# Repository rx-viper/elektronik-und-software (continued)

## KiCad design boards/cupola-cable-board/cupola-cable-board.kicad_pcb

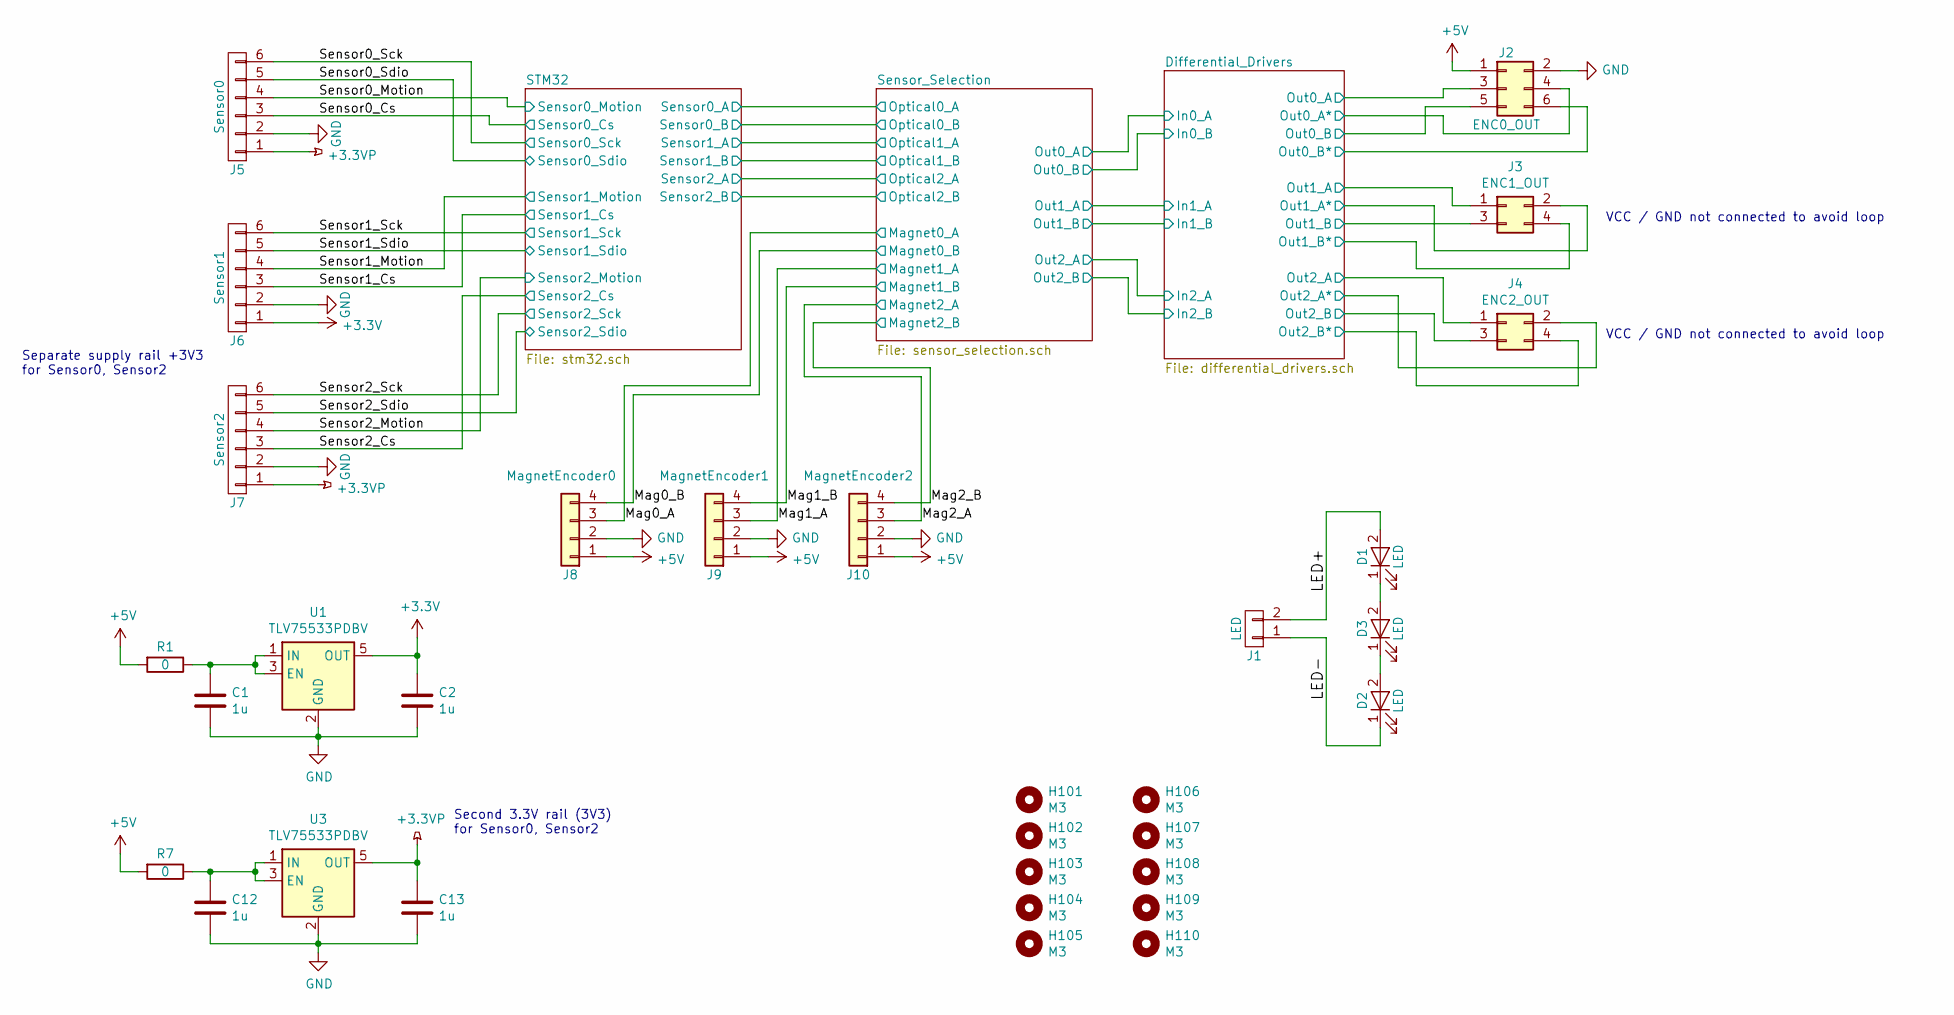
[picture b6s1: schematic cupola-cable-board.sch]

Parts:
C1, C2, C12, C13: 1u; C_0603_1608Metric
D1, D2, D3: LED; LW_G6SP_Handsoldering
H101, H102, H103, H104, H105, H106, H107, H108, H109, H110: M3; MountingHole_3.2mm_M3
J1: LED; PinHeader_1x02_P2.00mm_Vertical
J2: ENC0_OUT; PinHeader_2x03_P2.00mm_Vertical
J3: ENC1_OUT; PinHeader_2x02_P2.00mm_Vertical
J4: ENC2_OUT; PinHeader_2x02_P2.00mm_Vertical
J5: Sensor0; PinHeader_1x06_P2.00mm_Vertical
J6: Sensor1; PinHeader_1x06_P2.00mm_Vertical
J7: Sensor2; PinHeader_1x06_P2.00mm_Vertical
J8: MagnetEncoder0; PinHeader_1x04_P2.00mm_Vertical
J9: MagnetEncoder1; PinHeader_1x04_P2.00mm_Vertical
J10: MagnetEncoder2; PinHeader_1x04_P2.00mm_Vertical
R1, R7: 0; R_0603_1608Metric
U1, U3: TLV75533PDBV; SOT-23-5

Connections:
+3.3VP: C13.1, J5.1, J7.1, U3.5 (OUT)
+3V3: C2.1, J6.1, U1.5 (OUT); also elsewhere on the board
+5V: J2.1, J8.1, J9.1, J10.1, R1.2, R7.2; also elsewhere on the board
/Differential_Drivers/Out0_A: J2.3; also elsewhere on the board
/Differential_Drivers/Out0_A*: J2.4; also elsewhere on the board
/Differential_Drivers/Out0_B: J2.5; also elsewhere on the board
/Differential_Drivers/Out0_B*: J2.6; also elsewhere on the board
/Differential_Drivers/Out1_A: J3.1; also elsewhere on the board
/Differential_Drivers/Out1_A*: J3.2; also elsewhere on the board
/Differential_Drivers/Out1_B: J3.3; also elsewhere on the board
/Differential_Drivers/Out1_B*: J3.4; also elsewhere on the board
/Differential_Drivers/Out2_A: J4.1; also elsewhere on the board
/Differential_Drivers/Out2_A*: J4.2; also elsewhere on the board
/Differential_Drivers/Out2_B: J4.3; also elsewhere on the board
/Differential_Drivers/Out2_B*: J4.4; also elsewhere on the board
/LED+: D1.2 (A), J1.2
/LED-: D2.1 (K), J1.1
/Mag0_A: J8.3; also elsewhere on the board
/Mag0_B: J8.4; also elsewhere on the board
/Mag1_A: J9.3; also elsewhere on the board
/Mag1_B: J9.4; also elsewhere on the board
/Mag2_A: J10.3; also elsewhere on the board
/Mag2_B: J10.4; also elsewhere on the board
/Sensor0_Cs: J5.3; also elsewhere on the board
/Sensor0_Motion: J5.4; also elsewhere on the board
/Sensor0_Sck: J5.6; also elsewhere on the board
/Sensor0_Sdio: J5.5; also elsewhere on the board
/Sensor1_Cs: J6.3; also elsewhere on the board
/Sensor1_Motion: J6.4; also elsewhere on the board
/Sensor1_Sck: J6.6; also elsewhere on the board
/Sensor1_Sdio: J6.5; also elsewhere on the board
/Sensor2_Cs: J7.3; also elsewhere on the board
/Sensor2_Motion: J7.4; also elsewhere on the board
/Sensor2_Sck: J7.6; also elsewhere on the board
/Sensor2_Sdio: J7.5; also elsewhere on the board
GND: C1.2, C2.2, C12.2, C13.2, J2.2, J5.2, J6.2, J7.2, J8.2, J9.2, J10.2, U1.2 (GND), U3.2 (GND); also elsewhere on the board
unnamed: C1.1, R1.1, U1.1 (IN), U1.3 (EN)
unnamed: C12.1, R7.1, U3.1 (IN), U3.3 (EN)
unnamed: D1.1 (K), D3.2 (A)
unnamed: D2.2 (A), D3.1 (K)

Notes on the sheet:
VCC / GND not connected to avoid loop
Second 3.3V rail (3V3) for Sensor0, Sensor2
Separate supply rail +3V3 for Sensor0, Sensor2

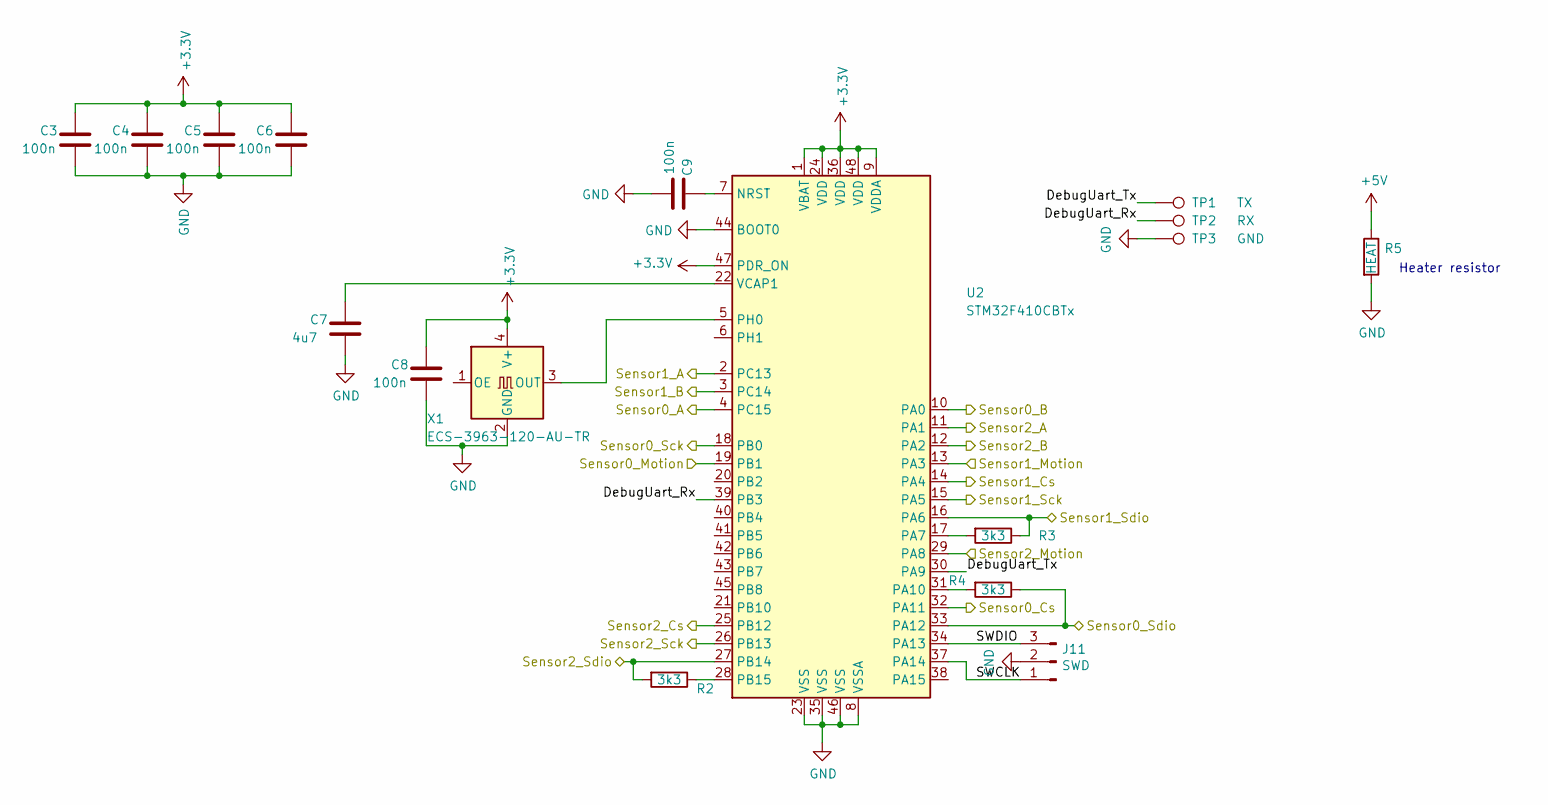
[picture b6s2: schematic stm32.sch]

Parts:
C3, C4, C5, C6, C8, C9: 100n; C_0603_1608Metric
C7: 4u7; C_0805_2012Metric
J11: SWD; PinHeader_1x03_P2.54mm_Vertical
R2, R3, R4: 3k3; R_0603_1608Metric
R5: HEAT; R_0805_2012Metric
TP1: TX; TestPoint_THTPad_D1.5mm_Drill0.7mm
TP2: RX; TestPoint_THTPad_D1.5mm_Drill0.7mm
TP3: GND; TestPoint_THTPad_D1.5mm_Drill0.7mm
U2: STM32F410CBTx; LQFP-48_7x7mm_P0.5mm
X1: ECS-3963-120-AU-TR; Oscillator_SMD_SeikoEpson_SG8002LB-4Pin_5.0x3.2mm

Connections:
+3V3: C3.1, C4.1, C5.1, C6.1, C8.1, U2.1 (VBAT), U2.9 (VDDA), U2.24 (VDD), U2.36 (VDD), U2.47 (PDR_ON), U2.48 (VDD), X1.4 (V+); also elsewhere on the board
+5V: R5.1; also elsewhere on the board
/STM32/DebugUart_Rx: TP2.1, U2.39 (PB3)
/STM32/DebugUart_Tx: TP1.1, U2.30 (PA9)
/STM32/SWCLK: J11.1, U2.37 (PA14)
/STM32/SWDIO: J11.3, U2.34 (PA13)
/Sensor0_Cs: U2.32 (PA11); also elsewhere on the board
/Sensor0_Motion: U2.19 (PB1); also elsewhere on the board
/Sensor0_Sck: U2.18 (PB0); also elsewhere on the board
/Sensor0_Sdio: R4.1, U2.33 (PA12); also elsewhere on the board
/Sensor1_Cs: U2.14 (PA4); also elsewhere on the board
/Sensor1_Motion: U2.13 (PA3); also elsewhere on the board
/Sensor1_Sck: U2.15 (PA5); also elsewhere on the board
/Sensor1_Sdio: R3.1, U2.16 (PA6); also elsewhere on the board
/Sensor2_Cs: U2.25 (PB12); also elsewhere on the board
/Sensor2_Motion: U2.29 (PA8); also elsewhere on the board
/Sensor2_Sck: U2.26 (PB13); also elsewhere on the board
/Sensor2_Sdio: R2.2, U2.27 (PB14); also elsewhere on the board
/Sensor_Selection/Optical0_A: U2.4 (PC15); also elsewhere on the board
/Sensor_Selection/Optical0_B: U2.10 (PA0); also elsewhere on the board
/Sensor_Selection/Optical1_A: U2.2 (PC13); also elsewhere on the board
/Sensor_Selection/Optical1_B: U2.3 (PC14); also elsewhere on the board
/Sensor_Selection/Optical2_A: U2.11 (PA1); also elsewhere on the board
/Sensor_Selection/Optical2_B: U2.12 (PA2); also elsewhere on the board
GND: C3.2, C4.2, C5.2, C6.2, C7.2, C8.2, C9.2, J11.2, R5.2, TP3.1, U2.8 (VSSA), U2.23 (VSS), U2.35 (VSS), U2.44 (BOOT0), U2.46 (VSS), X1.2 (GND); also elsewhere on the board
unnamed: C7.1, U2.22 (VCAP1)
unnamed: C9.1, U2.7 (NRST)
unnamed: R2.1, U2.28 (PB15)
unnamed: R3.2, U2.17 (PA7)
unnamed: R4.2, U2.31 (PA10)
unnamed: U2.5 (PH0), X1.3 (OUT)

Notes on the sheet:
Heater resistor

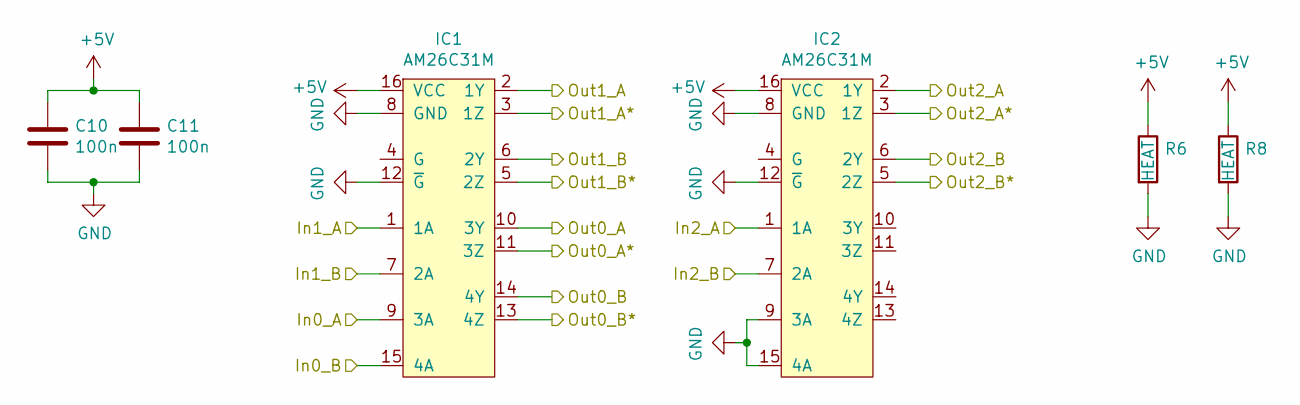
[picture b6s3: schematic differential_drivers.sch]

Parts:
C10, C11: 100n; C_0603_1608Metric
IC1, IC2: AM26C31M; SOIC-16_3.9x9.9mm_P1.27mm; Farnell 4975637
R6, R8: HEAT; R_0805_2012Metric

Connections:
+5V: C10.1, C11.1, IC1.16 (VCC), IC2.16 (VCC), R6.1, R8.1; also elsewhere on the board
/Differential_Drivers/In0_A: IC1.9 (3A); also elsewhere on the board
/Differential_Drivers/In0_B: IC1.15 (4A); also elsewhere on the board
/Differential_Drivers/In1_A: IC1.1 (1A); also elsewhere on the board
/Differential_Drivers/In1_B: IC1.7 (2A); also elsewhere on the board
/Differential_Drivers/In2_A: IC2.1 (1A); also elsewhere on the board
/Differential_Drivers/In2_B: IC2.7 (2A); also elsewhere on the board
/Differential_Drivers/Out0_A: IC1.10 (3Y); also elsewhere on the board
/Differential_Drivers/Out0_A*: IC1.11 (3Z); also elsewhere on the board
/Differential_Drivers/Out0_B: IC1.14 (4Y); also elsewhere on the board
/Differential_Drivers/Out0_B*: IC1.13 (4Z); also elsewhere on the board
/Differential_Drivers/Out1_A: IC1.2 (1Y); also elsewhere on the board
/Differential_Drivers/Out1_A*: IC1.3 (1Z); also elsewhere on the board
/Differential_Drivers/Out1_B: IC1.6 (2Y); also elsewhere on the board
/Differential_Drivers/Out1_B*: IC1.5 (2Z); also elsewhere on the board
/Differential_Drivers/Out2_A: IC2.2 (1Y); also elsewhere on the board
/Differential_Drivers/Out2_A*: IC2.3 (1Z); also elsewhere on the board
/Differential_Drivers/Out2_B: IC2.6 (2Y); also elsewhere on the board
/Differential_Drivers/Out2_B*: IC2.5 (2Z); also elsewhere on the board
GND: C10.2, C11.2, IC1.8 (GND), IC1.12 (~G), IC2.8 (GND), IC2.9 (3A), IC2.12 (~G), IC2.15 (4A), R6.2, R8.2; also elsewhere on the board

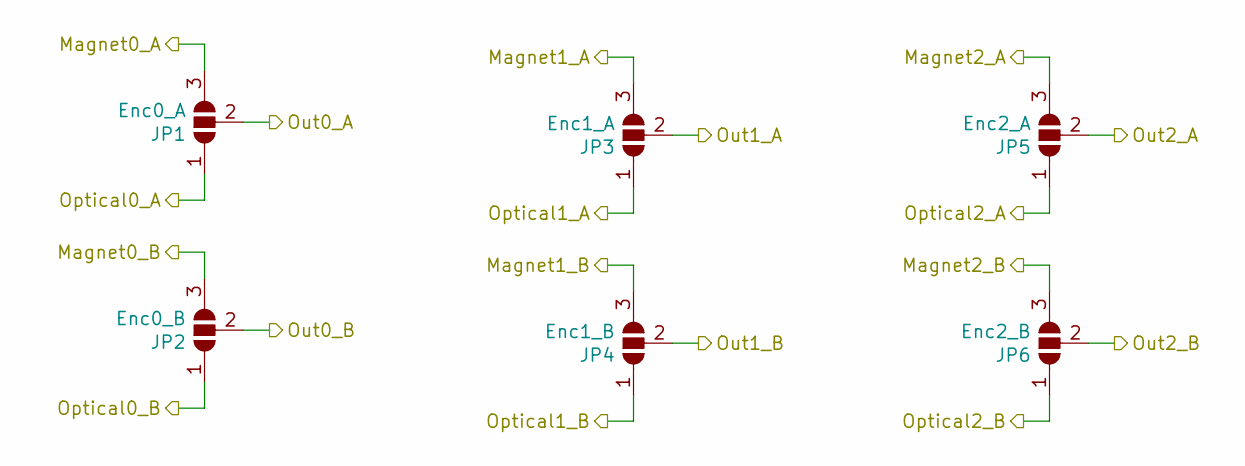
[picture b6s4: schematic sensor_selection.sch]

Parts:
JP1: Enc0_A; SolderJumper-3_P1.3mm_Open_RoundedPad1.0x1.5mm
JP2: Enc0_B; SolderJumper-3_P1.3mm_Open_RoundedPad1.0x1.5mm
JP3: Enc1_A; SolderJumper-3_P1.3mm_Open_RoundedPad1.0x1.5mm
JP4: Enc1_B; SolderJumper-3_P1.3mm_Open_RoundedPad1.0x1.5mm
JP5: Enc2_A; SolderJumper-3_P1.3mm_Open_RoundedPad1.0x1.5mm
JP6: Enc2_B; SolderJumper-3_P1.3mm_Open_RoundedPad1.0x1.5mm

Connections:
/Differential_Drivers/In0_A: JP1.2 (C); also elsewhere on the board
/Differential_Drivers/In0_B: JP2.2 (C); also elsewhere on the board
/Differential_Drivers/In1_A: JP3.2 (C); also elsewhere on the board
/Differential_Drivers/In1_B: JP4.2 (C); also elsewhere on the board
/Differential_Drivers/In2_A: JP5.2 (C); also elsewhere on the board
/Differential_Drivers/In2_B: JP6.2 (C); also elsewhere on the board
/Mag0_A: JP1.3 (B); also elsewhere on the board
/Mag0_B: JP2.3 (B); also elsewhere on the board
/Mag1_A: JP3.3 (B); also elsewhere on the board
/Mag1_B: JP4.3 (B); also elsewhere on the board
/Mag2_A: JP5.3 (B); also elsewhere on the board
/Mag2_B: JP6.3 (B); also elsewhere on the board
/Sensor_Selection/Optical0_A: JP1.1 (A); also elsewhere on the board
/Sensor_Selection/Optical0_B: JP2.1 (A); also elsewhere on the board
/Sensor_Selection/Optical1_A: JP3.1 (A); also elsewhere on the board
/Sensor_Selection/Optical1_B: JP4.1 (A); also elsewhere on the board
/Sensor_Selection/Optical2_A: JP5.1 (A); also elsewhere on the board
/Sensor_Selection/Optical2_B: JP6.1 (A); also elsewhere on the board

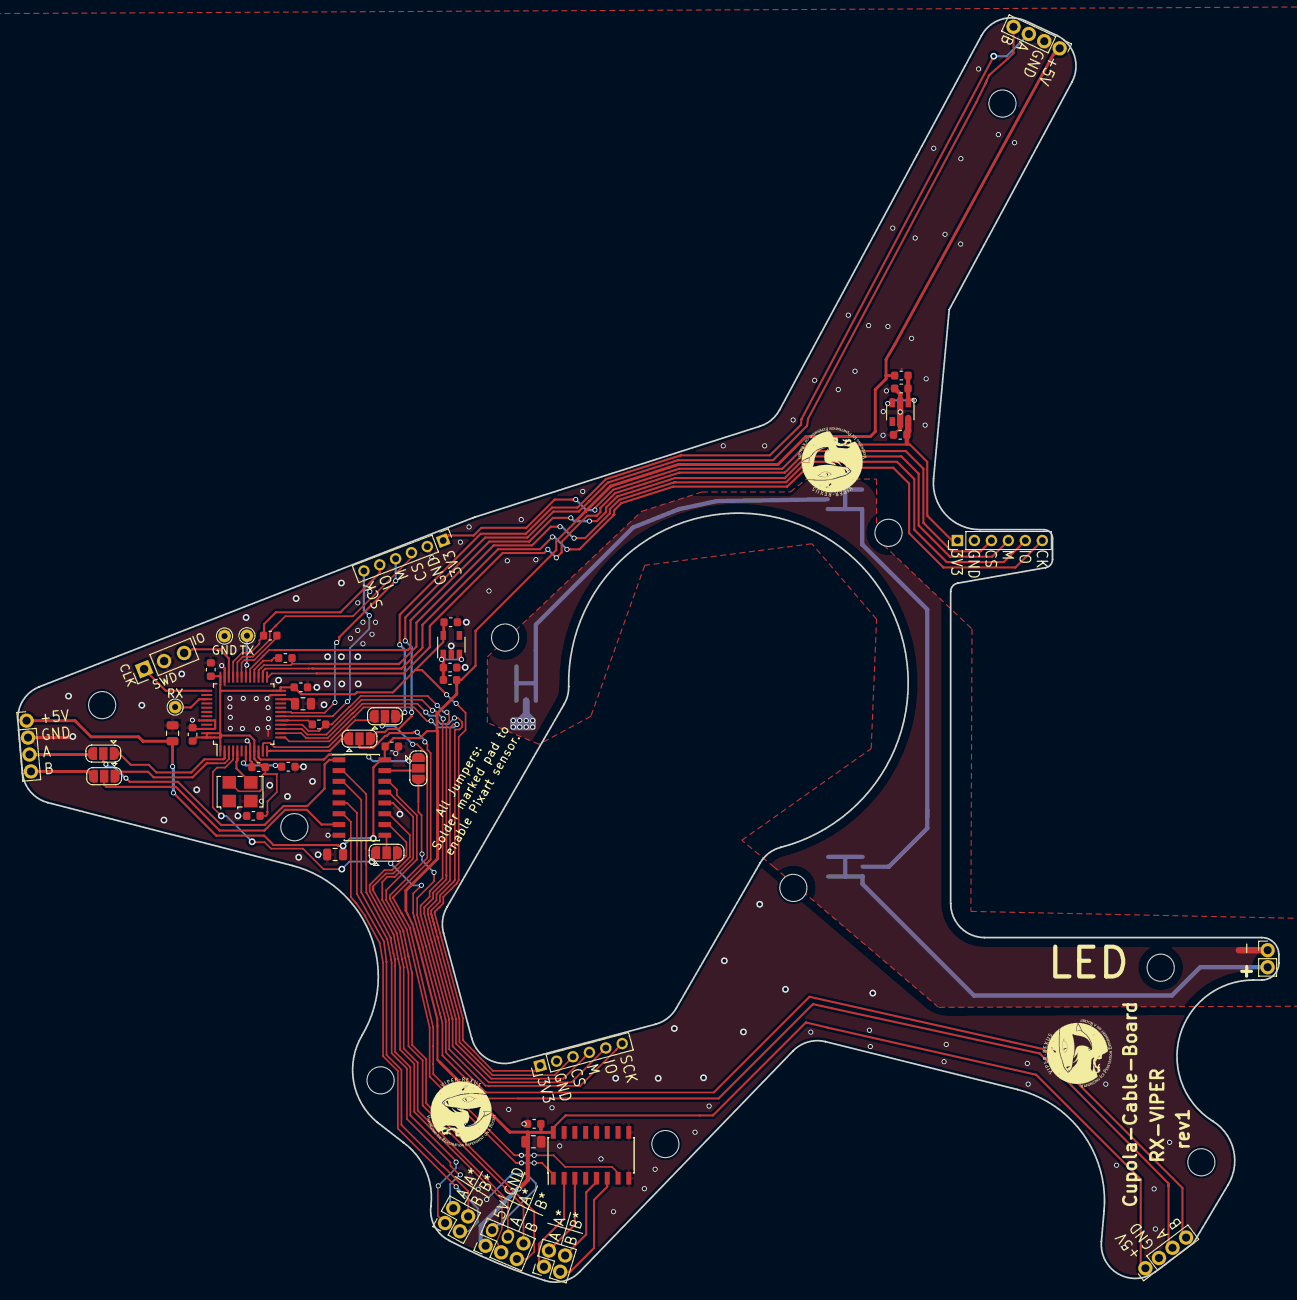
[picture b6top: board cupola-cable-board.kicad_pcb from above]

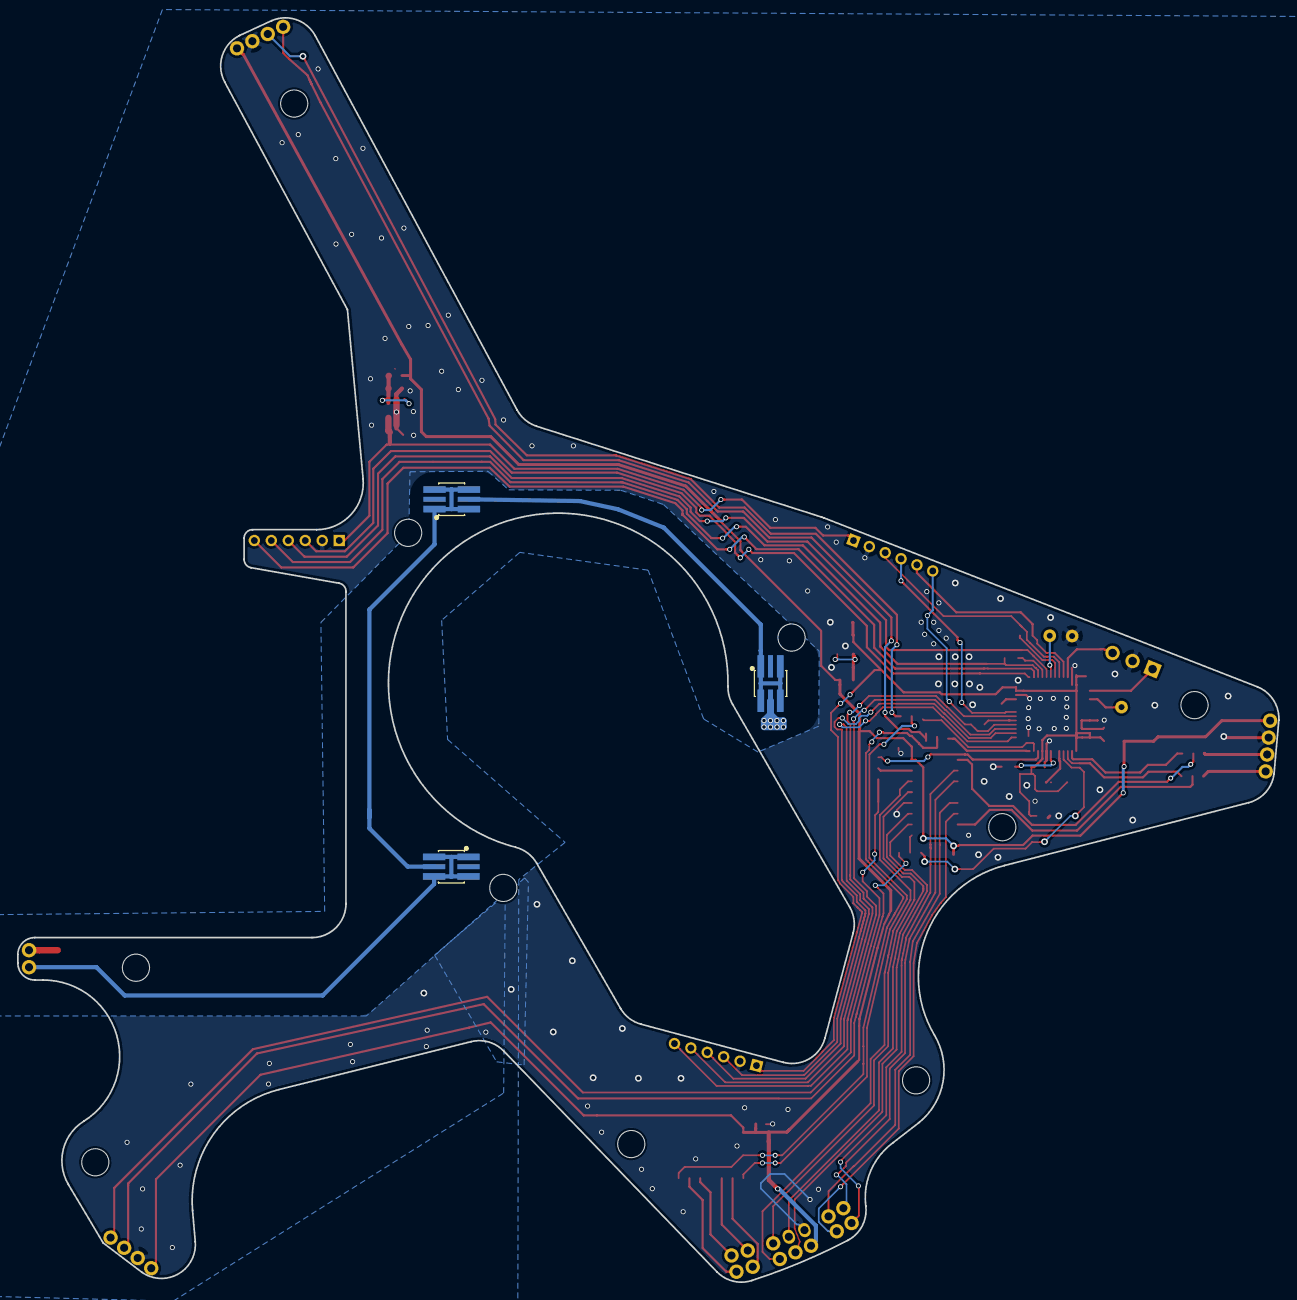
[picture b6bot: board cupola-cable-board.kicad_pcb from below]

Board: 2 copper layers, 148.5 x 148.9 mm, 60 parts (3 on the bottom side), 62 nets.

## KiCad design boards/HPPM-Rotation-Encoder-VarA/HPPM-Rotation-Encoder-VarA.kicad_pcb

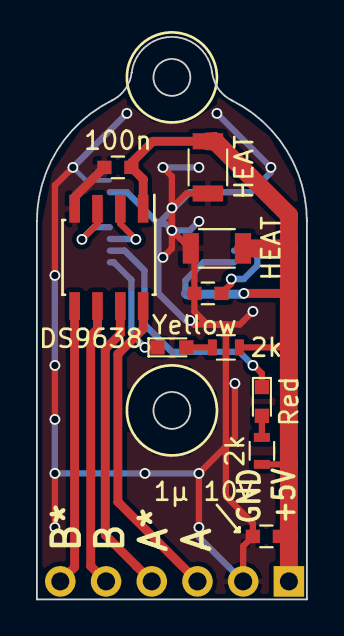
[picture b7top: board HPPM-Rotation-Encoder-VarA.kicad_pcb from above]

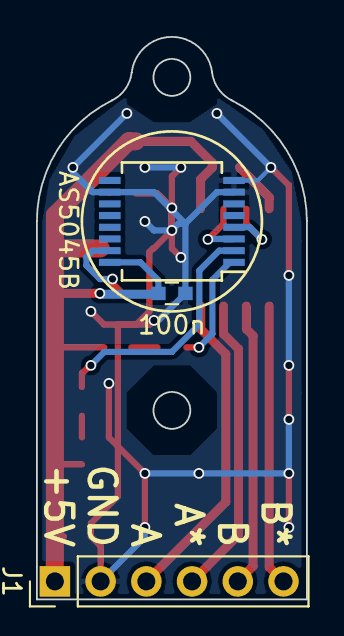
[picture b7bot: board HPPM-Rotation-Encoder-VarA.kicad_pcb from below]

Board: 2 copper layers, 15.0 x 31.2 mm, 13 parts (3 on the bottom side), 13 nets.

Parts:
C1, C3: 100n; C_0603
C2: 4µ7 6V3; C_0603
C4: 1µ 10V; C_0603
D1: Yellow; LED_0603
D2: Red; LED_0603
J1: CONN; Pin_Header_Straight_1x06_Pitch2.54mm
R1, R2: 2k; R_0603
R3, R4: HEAT; R_1206
U1: AS5045B; SSOP-16_5.3x6.2mm_Pitch0.65mm
U2: DS9638; SOIC-8_3.9x4.9mm_Pitch1.27mm

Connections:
+5V: C1.1, C3.1, C4.1, J1.1, R1.2, R2.2, R3.1, R4.1, U1.16, U2.1
/A: J1.3, U2.8
/A*: J1.4, U2.7
/B: J1.5, U2.6
/B*: J1.6, U2.5
/_A: U1.3, U2.2
/_B: U1.4, U2.3
GND: C1.2, C2.2, C3.2, C4.2, J1.2, R3.2, R4.2, U1.7, U1.8, U1.10, U2.4
unnamed: C2.1, U1.15
unnamed: D1.1, U1.1
unnamed: D1.2, R1.1
unnamed: D2.1, U1.2
unnamed: D2.2, R2.1

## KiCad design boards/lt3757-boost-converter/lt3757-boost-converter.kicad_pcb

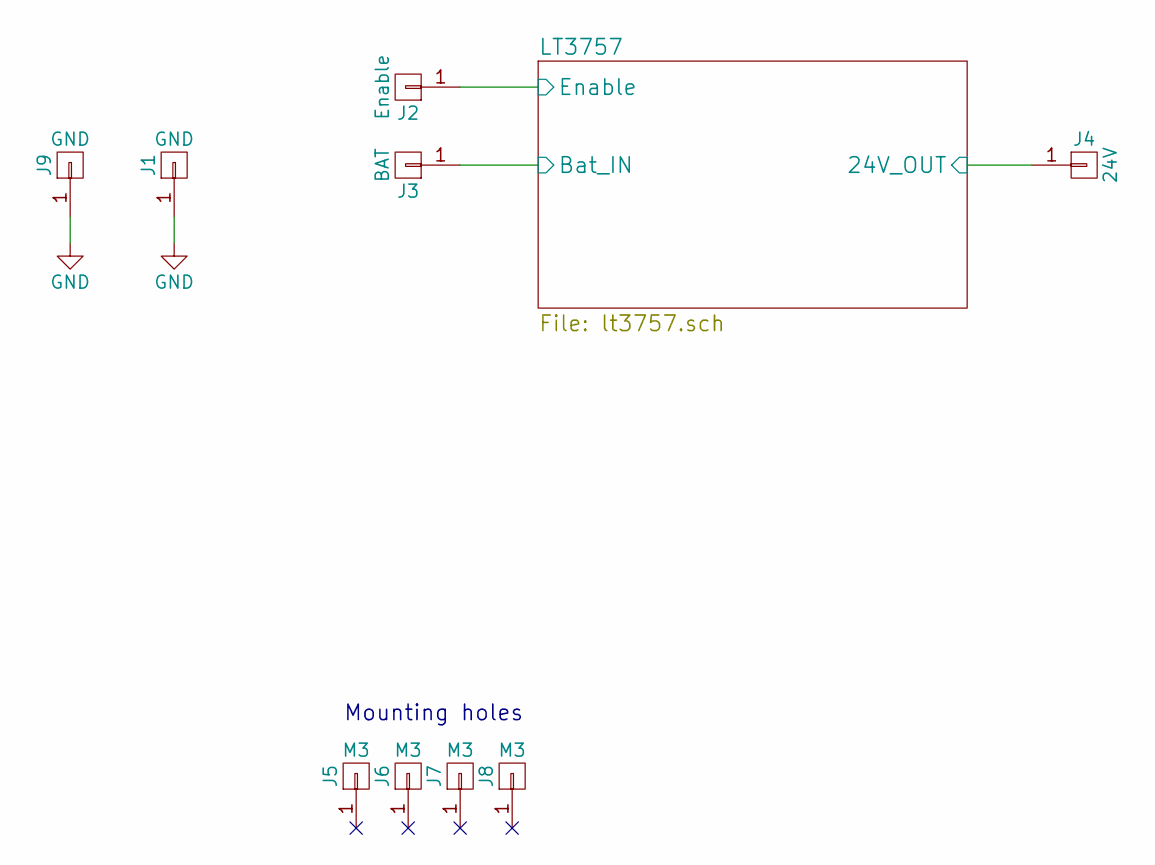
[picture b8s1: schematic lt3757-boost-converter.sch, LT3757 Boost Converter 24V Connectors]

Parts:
J1, J9: GND; MountingHole_3.2mm_M3_Pad
J2: Enable; Measurement_Point_Round-SMD-Pad_Small
J3: BAT; MountingHole_3.2mm_M3_Pad
J4: 24V; MountingHole_3.2mm_M3_Pad
J5, J6, J7, J8: M3; MountingHole_3.2mm_M3

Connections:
/LT3757/24V_OUT: J4.1; also elsewhere on the board
/LT3757/Bat_IN: J3.1; also elsewhere on the board
/LT3757/Enable: J2.1; also elsewhere on the board
GND: J1.1, J9.1; also elsewhere on the board

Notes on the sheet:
Mounting holes

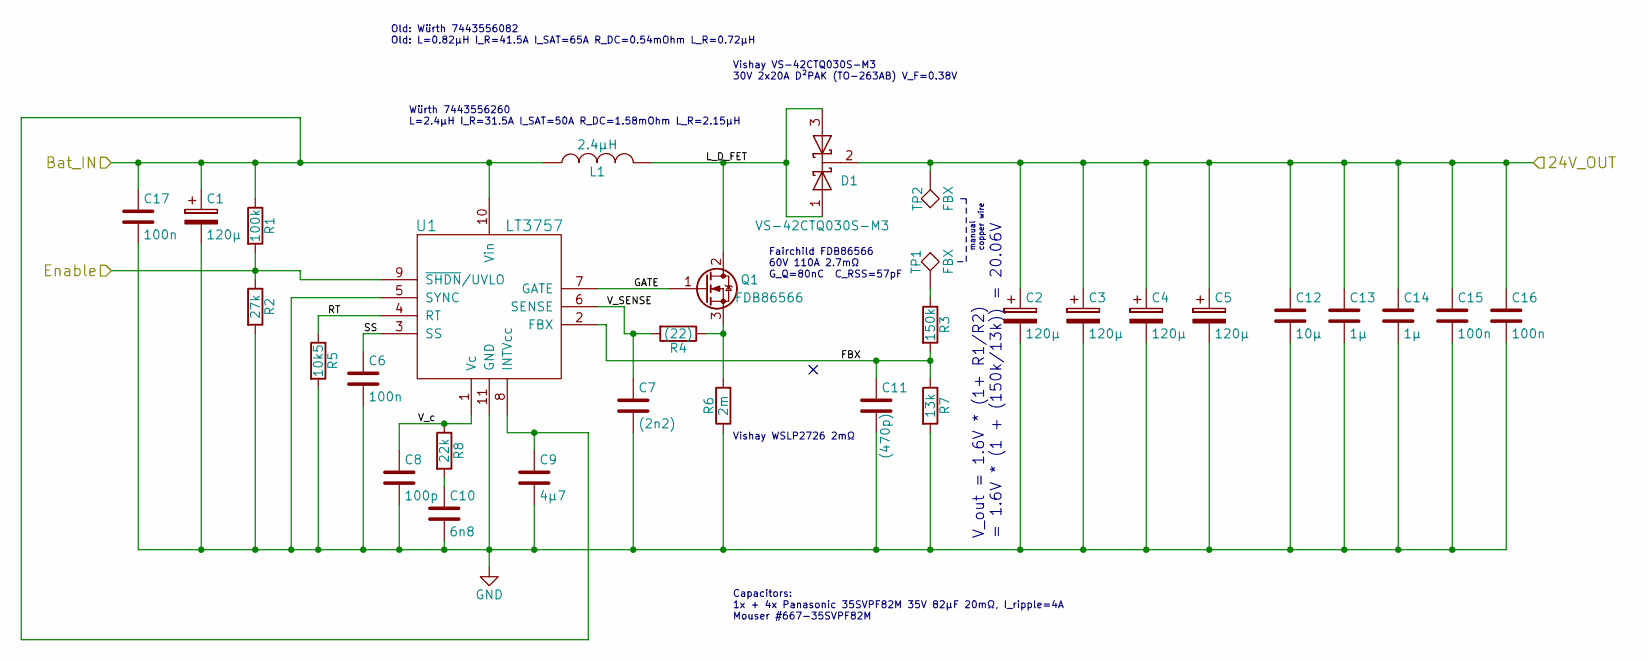
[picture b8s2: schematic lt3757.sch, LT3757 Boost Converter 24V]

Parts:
C1, C2, C3, C4, C5: 120µ; CP_Elec_10x10.5
C6, C15, C16, C17: 100n; C_0603_HandSoldering
C7: (2n2); C_0603_HandSoldering
C8: 100p; C_0603_HandSoldering
C9: 4µ7; C_0805_HandSoldering
C10: 6n8; C_0603_HandSoldering
C11: (470p); C_0603_HandSoldering
C12: 10µ; C_0603_HandSoldering
C13, C14: 1µ; C_0603_HandSoldering
D1: VS-42CTQ030S-M3; TO-263-3Lead
L1: 2.4µH; Inductor_Wurth_HCI-1890
Q1: FDB86566; TO-263-3Lead
R1: 100k; R_0603_HandSoldering
R2: 27k; R_0603_HandSoldering
R3: 150k; R_0603_HandSoldering
R4: (22); R_0603_HandSoldering
R5: 10k5; R_0603_HandSoldering
R6: 2m; WSLP2726
R7: 13k; R_0603_HandSoldering
R8: 22k; R_0603_HandSoldering
TP1, TP2: FBX; Measurement_Point_Round-SMD-Pad_Small
U1: LT3757; MSOP-10-1EP_3x3mm_Pitch0.5mm

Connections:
/LT3757/24V_OUT: C2.1, C3.1, C4.1, C5.1, C12.1, C13.1, C14.1, C15.1, C16.1, D1.2 (K), TP2.1; also elsewhere on the board
/LT3757/Bat_IN: C1.1, C9.1, C17.1, L1.1, R1.1, U1.8 (INTVcc), U1.10 (Vin); also elsewhere on the board
/LT3757/Enable: R1.2, R2.1, U1.9 (~SHDN~/UVLO); also elsewhere on the board
/LT3757/FBX: C11.1, R3.2, R7.1, U1.2 (FBX)
/LT3757/GATE: Q1.1 (G), U1.7 (GATE)
/LT3757/L_D_FET: D1.1 (A), D1.3 (A), L1.2, Q1.2 (D)
/LT3757/RT: R5.1, U1.4 (RT)
/LT3757/SS: C6.1, U1.3 (SS)
/LT3757/V_SENSE: C7.1, R4.2, U1.6 (SENSE)
/LT3757/V_c: C8.1, R8.1, U1.1 (Vc)
GND: C1.2, C2.2, C3.2, C4.2, C5.2, C6.2, C7.2, C8.2, C9.2, C10.2, C11.2, C12.2, C13.2, C14.2, C15.2, C16.2, C17.2, R2.2, R5.2, R6.1, R7.2, U1.5 (SYNC), U1.11 (GND); also elsewhere on the board
unnamed: C10.1, R8.2
unnamed: Q1.3 (S), R4.1, R6.2
unnamed: R3.1, TP1.1

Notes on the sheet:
Würth 7443556260 L=2.4µH I_R=31.5A I_SAT=50A R_DC=1.58mOhm L_R=2.15µH
Vishay VS-42CTQ030S-M3 30V 2x20A D²PAK (TO-263AB) V_F=0.38V
Capacitors: 1x + 4x Panasonic 35SVPF82M 35V 82µF 20mΩ, I_ripple=4A Mouser #667-35SVPF82M
Vishay WSLP2726 2mΩ
Fairchild FDB86566 60V 110A 2.7mΩ G_Q=80nC C_RSS=57pF
Old: Würth 7443556082 Old: L=0.82µH I_R=41.5A I_SAT=65A R_DC=0.54mOhm L_R=0.72µH
manual copper wire
V_out = 1.6V * (1+ R1/R2) = 1.6V * (1 + (150k/13k)) = 20.06V

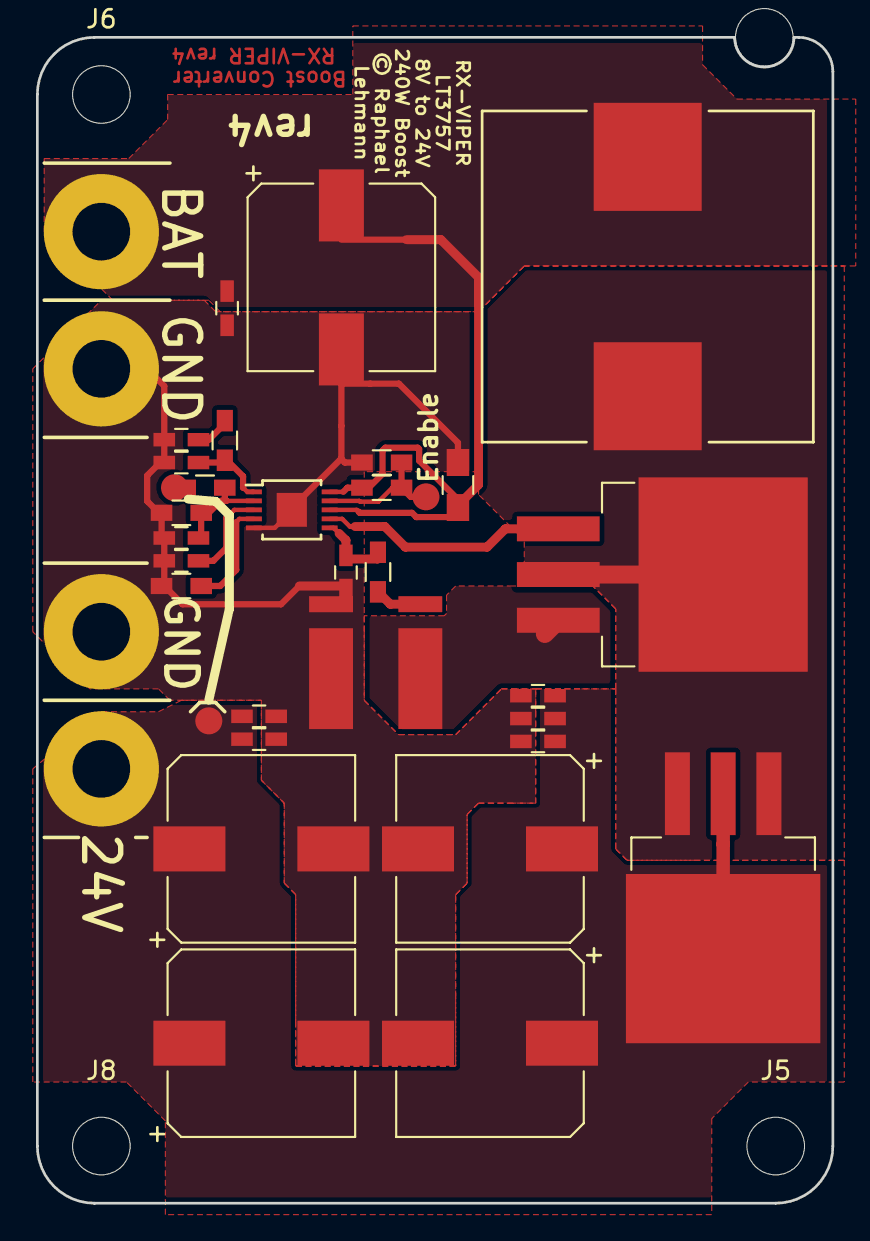
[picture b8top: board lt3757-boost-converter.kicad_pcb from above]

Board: 2 copper layers, 44.2 x 64.8 mm, 40 parts (0 on the bottom side), 14 nets.

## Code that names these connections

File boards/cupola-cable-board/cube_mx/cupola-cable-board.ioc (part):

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Mcu.Name=STM32F410C(8-B)Tx
Mcu.Package=LQFP48
Mcu.UserName=STM32F410CBTx
PA0-WKUP.GPIOParameters=GPIO_Label
PA0-WKUP.GPIO_Label=Sensor0_B
PA0-WKUP.Signal=GPIO_Output
PA1.GPIOParameters=GPIO_Label
PA1.GPIO_Label=Sensor2_A
PA1.Signal=GPIO_Output
PA10.Mode=Full_Duplex_Master
PA10.Signal=SPI5_MOSI
PA11.GPIOParameters=GPIO_Label
PA11.GPIO_Label=Sensor0_Cs
PA11.Signal=GPIO_Output
PA12.Mode=Full_Duplex_Master
PA12.Signal=SPI5_MISO
PA13.Mode=Serial_Wire
PA13.Signal=SYS_JTMS-SWDIO
PA14.Mode=Serial_Wire
PA14.Signal=SYS_JTCK-SWCLK
PA2.GPIOParameters=GPIO_Label
PA2.GPIO_Label=Sensor2_B
PA2.Signal=GPIO_Output
PA3.GPIOParameters=GPIO_Label
PA3.GPIO_Label=Sensor1_Motion
PA3.Signal=GPIO_Input
PA4.GPIOParameters=GPIO_Label
PA4.GPIO_Label=Sensor1_Cs
PA4.Signal=GPIO_Output
PA5.Mode=Full_Duplex_Master
PA5.Signal=SPI1_SCK
PA6.Mode=Full_Duplex_Master
PA6.Signal=SPI1_MISO
PA7.Mode=Full_Duplex_Master
PA7.Signal=SPI1_MOSI
PA8.GPIOParameters=GPIO_Label
PA8.GPIO_Label=Sensor2_Motion
PA8.Signal=GPIO_Input
PA9.Mode=Asynchronous
PA9.Signal=USART1_TX
PB0.Mode=Full_Duplex_Master
PB0.Signal=SPI5_SCK
PB1.GPIOParameters=GPIO_Label
PB1.GPIO_Label=Sensor0_Motion
PB1.Signal=GPIO_Input
PB12.GPIOParameters=GPIO_Label
PB12.GPIO_Label=Sensor2_Cs
PB12.Signal=GPIO_Output
PB13.Mode=Full_Duplex_Master
PB13.Signal=SPI2_SCK
PB14.Mode=Full_Duplex_Master
PB14.Signal=SPI2_MISO
PB15.Mode=Full_Duplex_Master
PB15.Signal=SPI2_MOSI
PB3.Mode=Asynchronous
PB3.Signal=USART1_RX
PC13-ANTI_TAMP.GPIOParameters=GPIO_Label
PC13-ANTI_TAMP.GPIO_Label=Sensor1_A
PC13-ANTI_TAMP.Signal=GPIO_Output
PC14-OSC32_IN.GPIOParameters=GPIO_Label
PC14-OSC32_IN.GPIO_Label=Sensor1_B
PC14-OSC32_IN.Signal=GPIO_Output
PC15-OSC32_OUT.GPIOParameters=GPIO_Label
PC15-OSC32_OUT.GPIO_Label=Sensor0_A
PC15-OSC32_OUT.Signal=GPIO_Output
PH0\ -\ OSC_IN.Mode=HSE-External-Oscillator
PH0\ -\ OSC_IN.Signal=RCC_OSC_IN
PH1\ -\ OSC_OUT.Mode=HSE-External-Oscillator
PH1\ -\ OSC_OUT.Signal=RCC_OSC_OUT
RCC.HSE_VALUE=12000000
RCC.SYSCLKFreq_VALUE=50000000
RCC.SYSCLKSource=RCC_SYSCLKSOURCE_PLLCLK
board=custom
